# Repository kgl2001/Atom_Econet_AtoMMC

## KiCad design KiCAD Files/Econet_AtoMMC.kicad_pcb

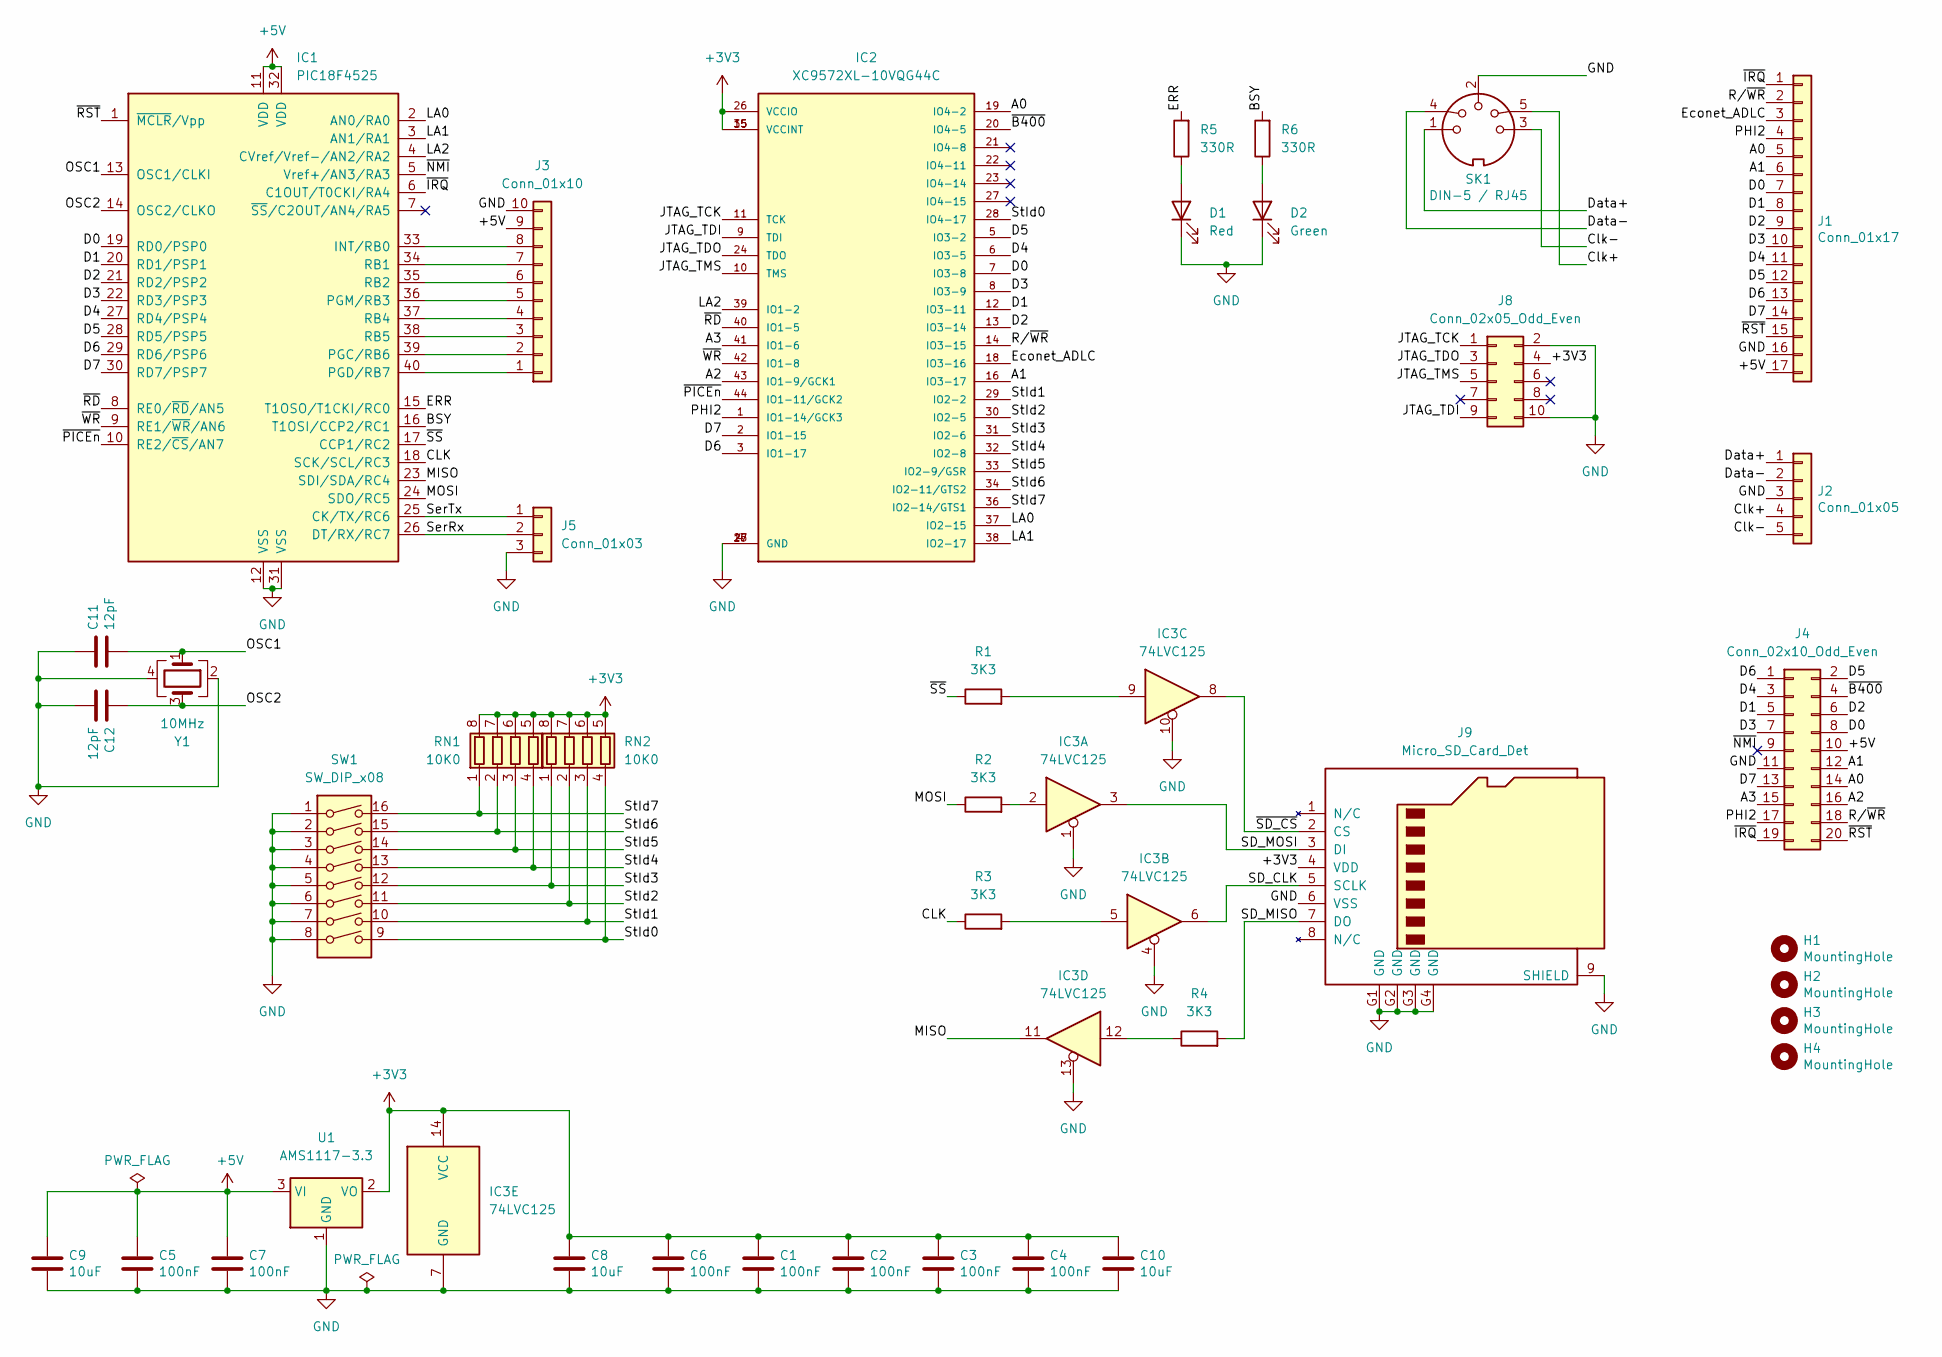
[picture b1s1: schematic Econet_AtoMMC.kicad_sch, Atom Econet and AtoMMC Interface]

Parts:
C1, C2, C3, C4, C5, C6, C7: 100nF; C_0603_1608Metric; JLC Part Number C14663
C8, C9, C10: 10uF; C_0805_2012Metric; JLC Part Number C15850
C11, C12: 12pF; C_0603_1608Metric; JLC Part Number C38523
D1: Red; LED_0603_1608Metric; JLC Part Number C2286
D2: Green; LED_0603_1608Metric; JLC Part Number C72043
H1, H2, H3, H4: MountingHole; MountingHole_2.7mm
IC1: PIC18F4525; DIP-40_W15.24mm_Socket
IC2: XC9572XL-10VQG44C; TQFP-44_10x10mm_P0.8mm
IC3: 74LVC125; TSSOP-14_4.4x5mm_P0.65mm; JLC Part Number C6059
J1: Conn_01x17; PinSocket_1x17_P2.54mm_Vertical
J2: Conn_01x05; PinSocket_1x05_P2.54mm_Vertical
J3: Conn_01x10; PinHeader_1x10_P2.54mm_Vertical
J4: Conn_02x10_Odd_Even; IDC-Header_2x10_P2.54mm_Vertical
J5: Conn_01x03; PinHeader_1x03_P2.54mm_Horizontal
J8: Conn_02x05_Odd_Even; PinHeader_2x05_P2.54mm_Vertical
J9: Micro_SD_Card_Det; SUNTECH_ST-TF-003A; JLC Part Number C266620
R1, R2, R3, R4: 3K3; R_0603_1608Metric; JLC Part Number C22978
R5, R6: 330R; R_0603_1608Metric; JLC Part Number C23138
RN1, RN2: 10K0; R_Array_Concave_4x0603; JLC Part Number C29718
SK1: DIN-5 / RJ45; CombinedDIN5RJ45PinHeader90Deg
SW1: SW_DIP_x08; SW_DIP_SPSTx08_Slide_Omron_A6S-810x_W8.9mm_P2.54mm; JLC Part Number C311837
U1: AMS1117-3.3; SOT-223-3_TabPin2; JLC Part Number C6186
Y1: 10MHz; Crystal_SMD_3225-4Pin_3.2x2.5mm; JLC Part Number C654941

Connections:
+3V3: C1.1, C2.1, C3.1, C4.1, C6.1, C8.1, C10.1, IC2.15 (VCCINT), IC2.26 (VCCIO), IC2.35 (VCCINT), IC3.14 (VCC), J8.4, J9.4 (VDD), RN1.5 (R4.2), RN1.6 (R3.2), RN1.7 (R2.2), RN1.8 (R1.2), RN2.5 (R4.2), RN2.6 (R3.2), RN2.7 (R2.2), RN2.8 (R1.2), U1.2 (VO)
+5V: C5.1, C7.1, C9.1, IC1.11 (VDD), IC1.32 (VDD), J1.17, J3.9, J4.10, U1.3 (VI)
/A0: IC2.19 (IO4-2), J1.5, J4.14
/A1: IC2.16 (IO3-17), J1.6, J4.12
/A2: IC2.43 (IO1-9/GCK1), J4.16
/A3: IC2.41 (IO1-6), J4.15
/BSY: IC1.16 (T1OSI/CCP2/RC1), R6.2
/CLK: IC1.18 (SCK/SCL/RC3), R3.1
/Clk+: J2.4, SK1.5
/Clk-: J2.5, SK1.3
/D0: IC1.19 (RD0/PSP0), IC2.7 (IO3-8), J1.7, J4.8
/D1: IC1.20 (RD1/PSP1), IC2.12 (IO3-11), J1.8, J4.5
/D2: IC1.21 (RD2/PSP2), IC2.13 (IO3-14), J1.9, J4.6
/D3: IC1.22 (RD3/PSP3), IC2.8 (IO3-9), J1.10, J4.7
/D4: IC1.27 (RD4/PSP4), IC2.6 (IO3-5), J1.11, J4.3
/D5: IC1.28 (RD5/PSP5), IC2.5 (IO3-2), J1.12, J4.2
/D6: IC1.29 (RD6/PSP6), IC2.3 (IO1-17), J1.13, J4.1
/D7: IC1.30 (RD7/PSP7), IC2.2 (IO1-15), J1.14, J4.13
/Data+: J2.1, SK1.1
/Data-: J2.2, SK1.4
/ERR: IC1.15 (T1OSO/T1CKI/RC0), R5.2
/Econet_ADLC: IC2.18 (IO3-16), J1.3
/JTAG_TCK: IC2.11 (TCK), J8.1
/JTAG_TDI: IC2.9 (TDI), J8.9
/JTAG_TDO: IC2.24 (TDO), J8.3
/JTAG_TMS: IC2.10 (TMS), J8.5
/LA0: IC1.2 (AN0/RA0), IC2.37 (IO2-15)
/LA1: IC1.3 (AN1/RA1), IC2.38 (IO2-17)
/LA2: IC1.4 (CVref/Vref-/AN2/RA2), IC2.39 (IO1-2)
/MISO: IC1.23 (SDI/SDA/RC4), IC3.11
/MOSI: IC1.24 (SDO/RC5), R2.1
/OSC1: C11.2, IC1.13 (OSC1/CLKI), Y1.1
/OSC2: C12.1, IC1.14 (OSC2/CLKO), Y1.3
/PHI2: IC2.1 (IO1-14/GCK3), J1.4, J4.17
/R/~WR: IC2.14 (IO3-15), J1.2, J4.18
/SD_CLK: IC3.6, J9.5 (SCLK)
/SD_MISO: J9.7 (DO), R4.2
/SD_MOSI: IC3.3, J9.3 (DI)
/SerRx: IC1.26 (DT/RX/RC7), J5.2
/SerTx: IC1.25 (CK/TX/RC6), J5.1
/StId0: IC2.28 (IO4-17), RN2.4 (R4.1), SW1.9
/StId1: IC2.29 (IO2-2), RN2.3 (R3.1), SW1.10
/StId2: IC2.30 (IO2-5), RN2.2 (R2.1), SW1.11
/StId3: IC2.31 (IO2-6), RN2.1 (R1.1), SW1.12
/StId4: IC2.32 (IO2-8), RN1.4 (R4.1), SW1.13
/StId5: IC2.33 (IO2-9/GSR), RN1.3 (R3.1), SW1.14
/StId6: IC2.34 (IO2-11/GTS2), RN1.2 (R2.1), SW1.15
/StId7: IC2.36 (IO2-14/GTS1), RN1.1 (R1.1), SW1.16
/~B400: IC2.20 (IO4-5), J4.4
/~IRQ: IC1.6 (C1OUT/T0CKI/RA4), J1.1, J4.19
/~NMI: IC1.5 (Vref+/AN3/RA3), J4.9
/~PICEn: IC1.10 (RE2/~CS/AN7), IC2.44 (IO1-11/GCK2)
/~RD: IC1.8 (RE0/~RD/AN5), IC2.40 (IO1-5)
/~RST: IC1.1 (~MCLR/Vpp), J1.15, J4.20
/~SD_CS: IC3.8, J9.2 (CS)
/~SS: IC1.17 (CCP1/RC2), R1.1
/~WR: IC1.9 (RE1/~WR/AN6), IC2.42 (IO1-8)
GND: C1.2, C2.2, C3.2, C4.2, C5.2, C6.2, C7.2, C8.2, C9.2, C10.2, C11.1, C12.2, D1.1 (K), D2.1 (K), IC1.12 (VSS), IC1.31 (VSS), IC2.4 (GND), IC2.17 (GND), IC2.25 (GND), IC3.1, IC3.4, IC3.7 (GND), IC3.10, IC3.13, J1.16, J2.3, J3.10, J4.11, J5.3, J8.2, J8.10, J9.6 (VSS), J9.9 (SHIELD), J9.G1 (GND), J9.G2 (GND), J9.G3 (GND), J9.G4 (GND), SK1.2, SW1.1, SW1.2, SW1.3, SW1.4, SW1.5, SW1.6, SW1.7, SW1.8, U1.1 (GND), Y1.2, Y1.4
unnamed: D1.2 (A), R5.1
unnamed: D2.2 (A), R6.1
unnamed: IC1.33 (INT/RB0), J3.8
unnamed: IC1.39 (PGC/RB6), J3.2
unnamed: IC1.40 (PGD/RB7), J3.1
unnamed: IC1.36 (PGM/RB3), J3.5
unnamed: IC1.34 (RB1), J3.7
unnamed: IC1.35 (RB2), J3.6
unnamed: IC1.37 (RB4), J3.4
unnamed: IC1.38 (RB5), J3.3
unnamed: IC3.2, R2.2
unnamed: IC3.5, R3.2
unnamed: IC3.9, R1.2
unnamed: IC3.12, R4.1

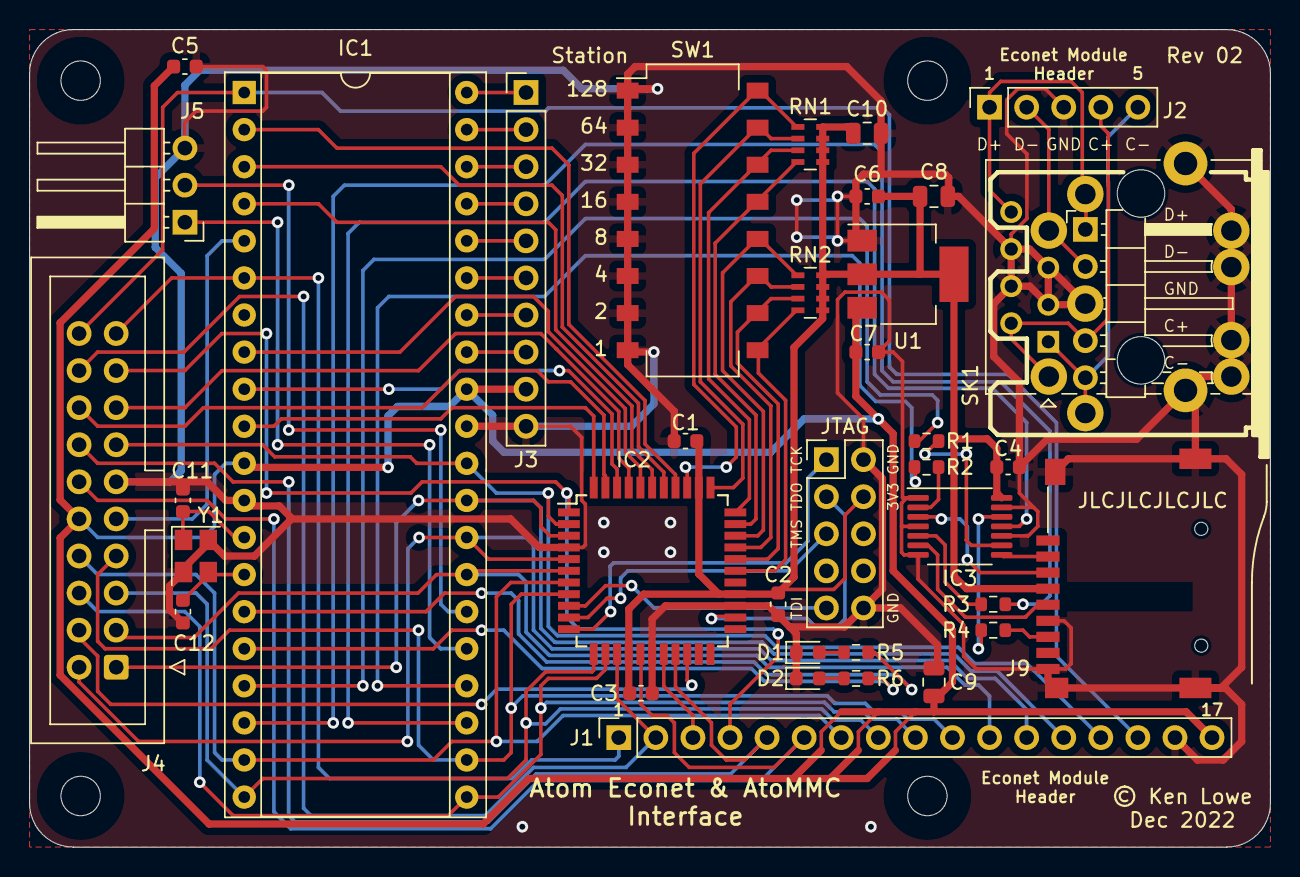
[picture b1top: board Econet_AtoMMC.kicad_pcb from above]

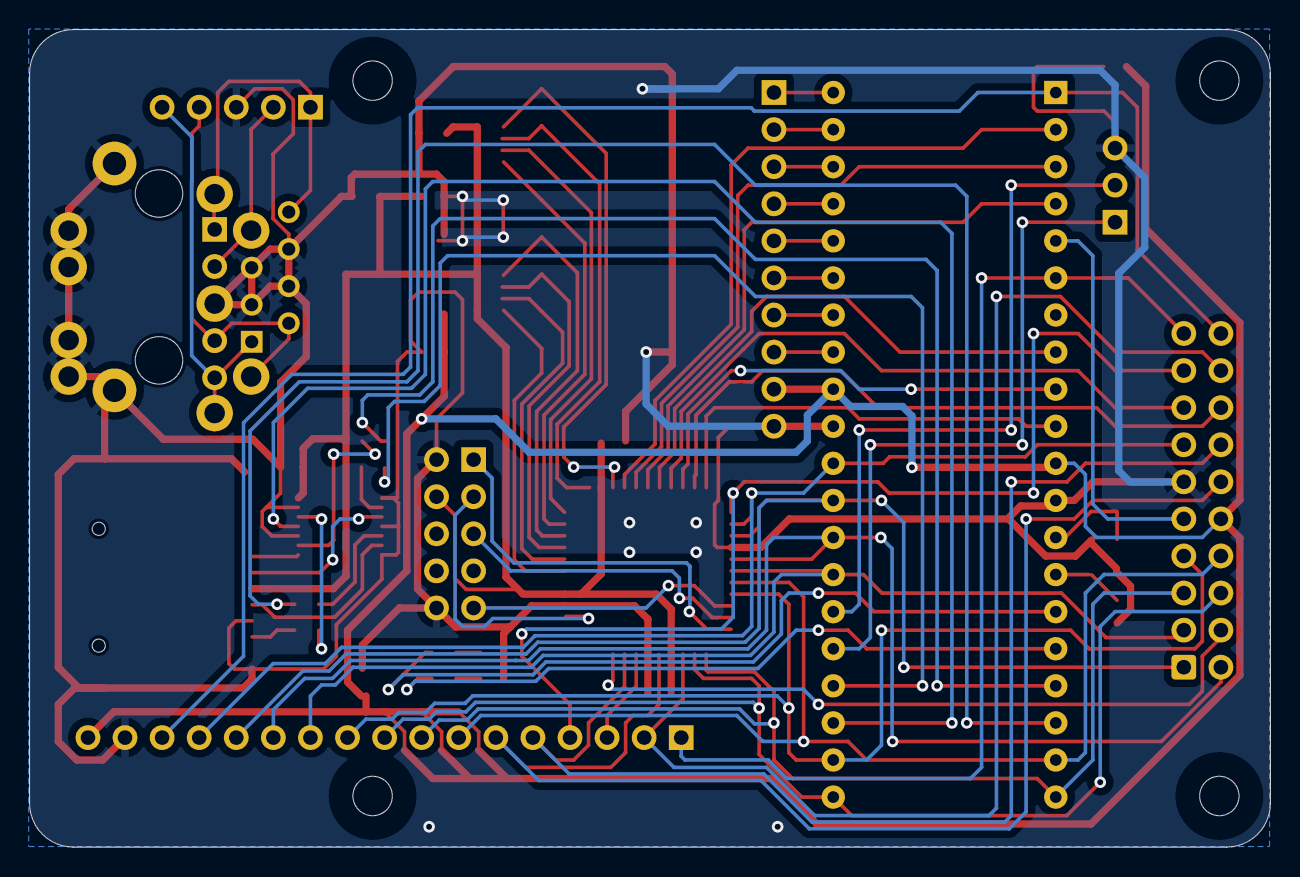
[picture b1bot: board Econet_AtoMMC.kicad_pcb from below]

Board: 2 copper layers, 85.0 x 56.0 mm, 40 parts (4 on the bottom side), 72 nets.

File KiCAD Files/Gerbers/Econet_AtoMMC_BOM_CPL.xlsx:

Designator | LCSC Part # | Footprint | JLCValue | Mid X | Mid Y | Rotation | Layer | Val | Package
C1 | C14663 | 0603 | 100nF | 134.84700000000001 | -84.245000000000005 | 180 | top | 100nF | C_0603_1608Metric
C2 | C14663 | 0603 | 100nF | 141.197 | -95.421000000000006 | -90 | top | 100nF | C_0603_1608Metric
C3 | C14663 | 0603 | 100nF | 131.79900000000001 | -101.517 | 0 | top | 100nF | C_0603_1608Metric
C4 | C14663 | 0603 | 100nF | 156.94499999999999 | -86.022999999999996 | 0 | top | 100nF | C_0603_1608Metric
C5 | C14663 | 0603 | 100nF | 100.557 | -58.591000000000001 | 0 | top | 100nF | C_0603_1608Metric
C6 | C14663 | 0603 | 100nF | 147.29300000000001 | -67.480999999999995 | 180 | top | 100nF | C_0603_1608Metric
C7 | C14663 | 0603 | 100nF | 147.29300000000001 | -78.149000000000001 | 0 | top | 100nF | C_0603_1608Metric
C8 | C15850 | 0805 | 10uF | 151.86500000000001 | -67.480999999999995 | 0 | top | 10uF | C_0805_2012Metric
C9 | C15850 | 0805 | 10uF | 151.86500000000001 | -100.755 | 90 | top | 10uF | C_0805_2012Metric
C10 | C15850 | 0805 | 10uF | 147.29300000000001 | -63.162999999999997 | 0 | top | 10uF | C_0805_2012Metric
C11 | C38523 | 0603 | 12pF | 100.4205 | -88.304000000000002 | -90 | top | 15pF | C_0603_1608Metric
C12 | C38523 | 0603 | 12pF | 100.4205 | -95.924000000000007 | -90 | top | 15pF | C_0603_1608Metric
D1 | C2286 | 0603 | Red | 143.22900000000001 | -98.722999999999999 | 0 | top | Red | LED_0603_1608Metric
D2 | C72043 | 0603 | Green | 143.22900000000001 | -100.501 | 0 | top | Green | LED_0603_1608Metric
IC3 | C6059 | TSSOP-14 | 74LVC125 | 153.643 | -90.087000000000003 | -90 | top | 74LVC125 | TSSOP-14_4.4x5mm_P0.65mm
J9 | C266620 | TF-115 | Micro_SD_Card_Det | 164.77500000000001 | -93.305000000000007 | 0 | top | Micro_SD_Card_Det | SUNTECH_ST-TF-003A
R1 | C22978 | 0603 | 3K3 | 151.357 | -84.245000000000005 | 0 | top | 3K3 | R_0603_1608Metric
R2 | C22978 | 0603 | 3K3 | 151.357 | -86.022999999999996 | 0 | top | 3K3 | R_0603_1608Metric
R3 | C22978 | 0603 | 3K3 | 155.929 | -95.421000000000006 | 180 | top | 3K3 | R_0603_1608Metric
R4 | C22978 | 0603 | 3K3 | 155.929 | -97.198999999999998 | 0 | top | 3K3 | R_0603_1608Metric
R5 | C23138 | 0603 | 330R | 146.53100000000001 | -98.722999999999999 | 0 | top | 330R | R_0603_1608Metric
R6 | C23138 | 0603 | 330R | 146.53100000000001 | -100.501 | 0 | top | 330R | R_0603_1608Metric
RN1 | C29718 | 0603_x4 | 10K0 | 143.39500000000001 | -63.924999999999997 | -90 | top | 10K0 | R_Array_Concave_4x0603
RN2 | C29718 | 0603_x4 | 10K0 | 143.39500000000001 | -74.084999999999994 | -90 | top | 10K0 | R_Array_Concave_4x0603
SW1 | C311837 | SW_DIP_SPSTx08 | SW_DIP_x08 | 135.33600000000001 | -69.126999999999995 | -90 | top | SW_DIP_x08 | SW_DIP_SPSTx08_Slide_Omron_A6S-810x_W8.9mm_P2.54mm
U1 | C6186 | SOT-223-3 | AMS1117-3.3 | 150.08699999999999 | -72.814999999999998 | 180 | top | AMS1117-3.3 | SOT-223-3_TabPin2
Y1 | C654941 | SMD-3225-4P | 10MHz | 101.3095 | -92.114000000000004 | -90 | top | 10MHz | Crystal_SMD_3225-4Pin_3.2x2.5mm

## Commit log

2022-12-20 Initial CPLD files
2022-12-20 Whitespace only
2022-12-20 Address decoding for Econet hardware
2023-01-06 Update comments
    Removed comments about future Econet code
2023-10-04 KiCAD Files - Initial Commit
2023-10-04 Added License file
2023-10-04 Added 3D Models
2023-10-04 Added compiled JED file
2023-10-04 Added PIC18F4525 firmware files

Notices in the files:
KiCAD Files/Econet_AtoMMC.kicad_pcb:
© Ken Lowe
